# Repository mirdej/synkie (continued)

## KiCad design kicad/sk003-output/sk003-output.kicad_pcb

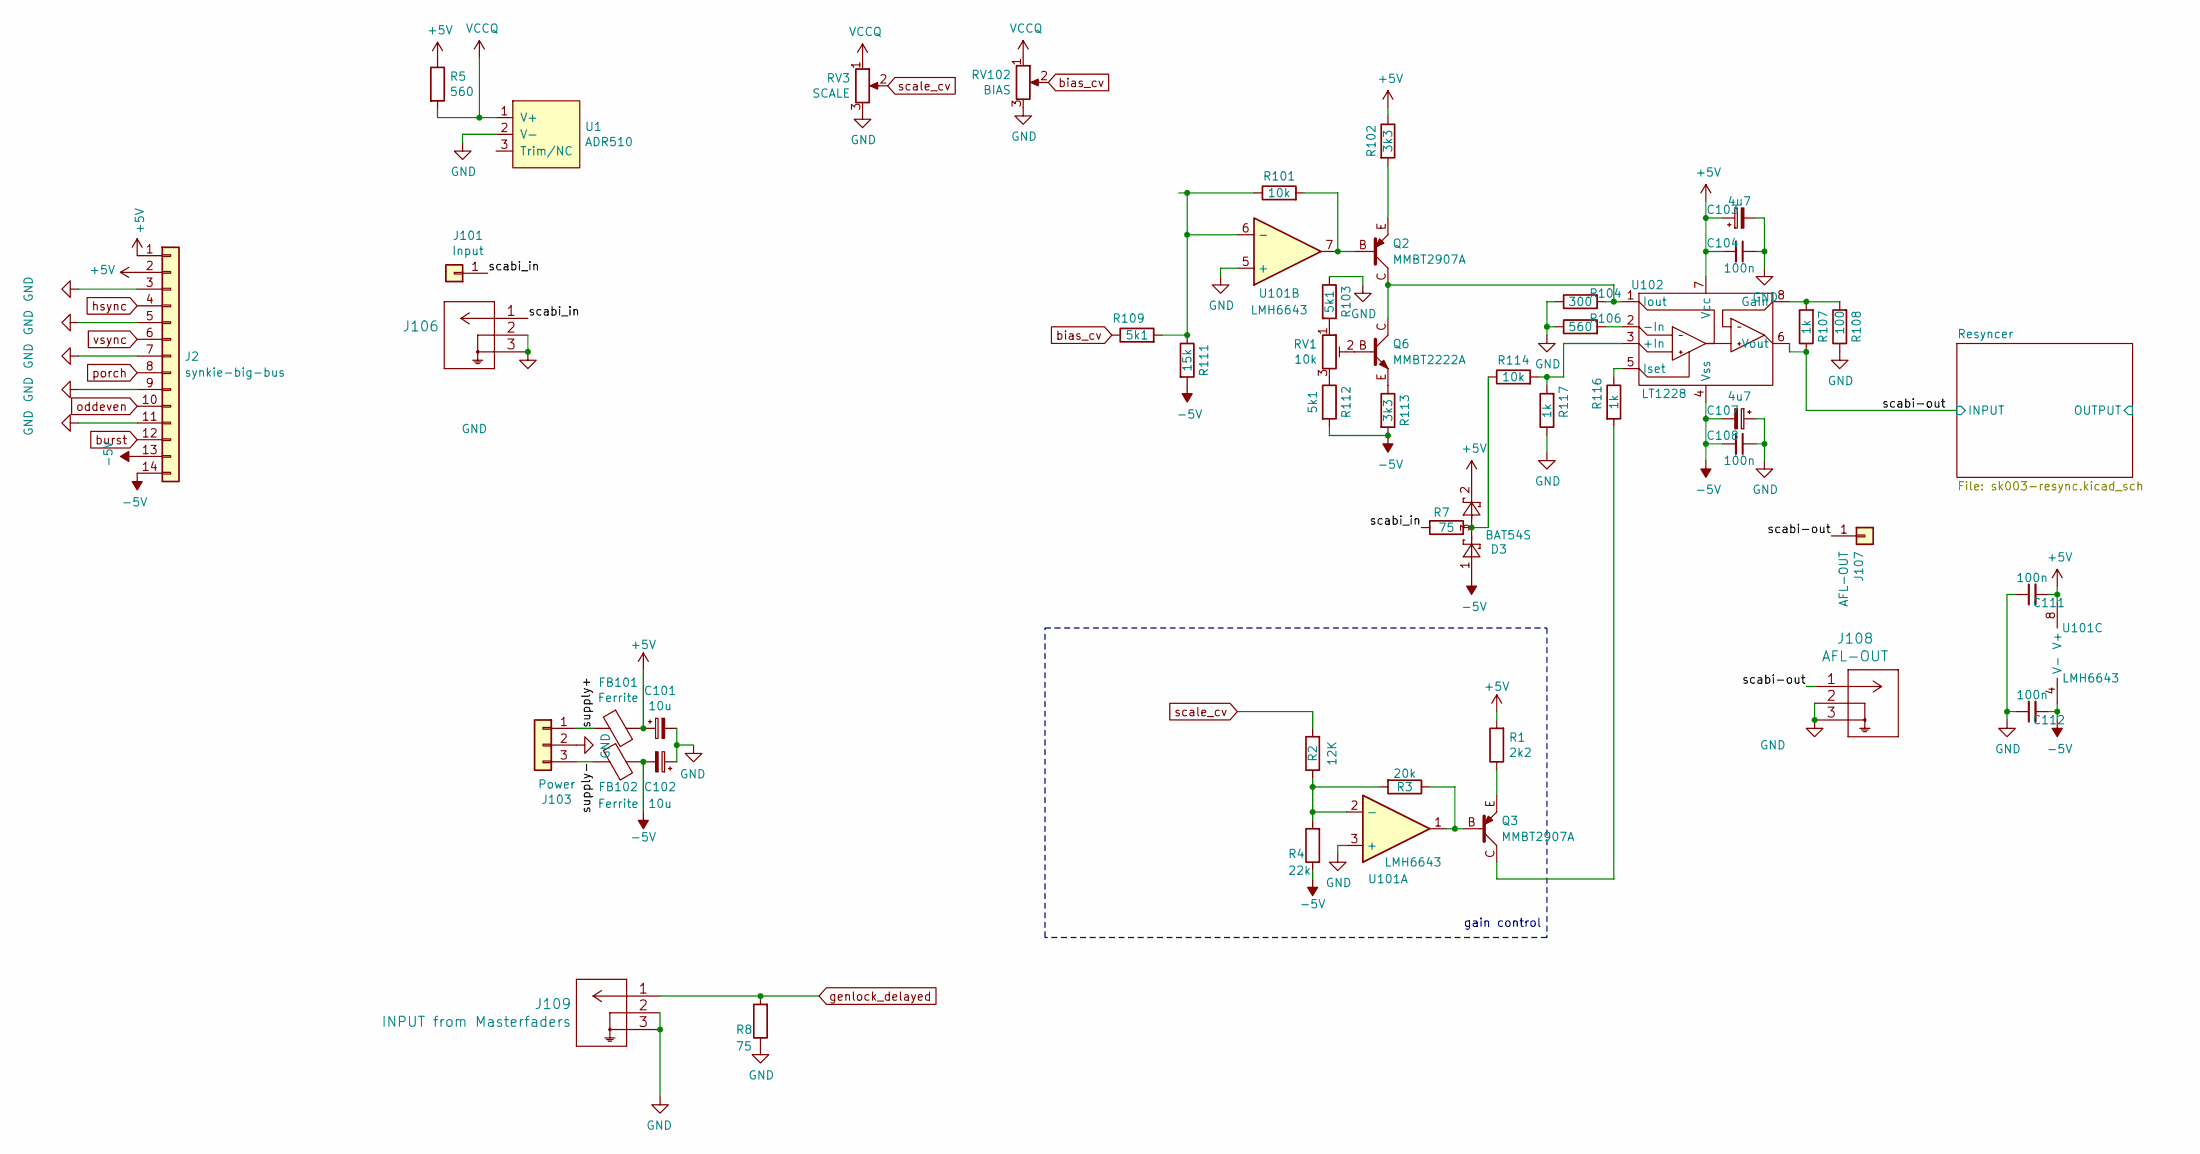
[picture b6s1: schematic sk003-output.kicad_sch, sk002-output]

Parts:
C101, C102: 10u; C_0805_2012Metric; LCSC C15850
C103, C107: 4u7; C_1206_3216Metric; LCSC C29823
C104, C108, C111, C112: 100n; C_0603_1608Metric; LCSC C14663
D3: BAT54S; SOT-23; LCSC C8592
FB101, FB102: Ferrite; L_0805_2012Metric_Pad1.15x1.40mm_HandSolder; LCSC C1017
J2: synkie-big-bus; IDC-Header_2x07_P2.54mm_Vertical
J101: Input; TestPoint_THTPad_D4.0mm_Drill2.0mm
J103: Power; Molex_KK-254_AE-6410-03A_1x03_P2.54mm_Vertical
J106: INPUT from Mixbus; TE_UMCC_2337019-1
J107: AFL-OUT; TestPoint_THTPad_D4.0mm_Drill2.0mm
J108: AFL-OUT; TE_UMCC_2337019-1; LCSC C5137195
J109: INPUT from Masterfaders; TE_UMCC_2337019-1; LCSC C5137195
Q2, Q3: MMBT2907A; SOT-23_BEC; LCSC C40752
Q6: MMBT2222A; SOT-23_BEC; LCSC C82460
R1: 2k2; R_0603_1608Metric; LCSC C4190
R2: 12K; R_0603_1608Metric; LCSC C22790
R3: 20k; R_0603_1608Metric; LCSC C4184
R4: 22k; R_0603_1608Metric; LCSC C31850
R5, R106: 560; R_0603_1608Metric; LCSC C23204
R7, R8: 75; R_0603_1608Metric; LCSC C4275
R101, R114: 10k; R_0603_1608Metric; LCSC C25804
R102, R113: 3k3; R_0603_1608Metric; LCSC C22978
R103, R109, R112: 5k1; R_0603_1608Metric; LCSC C23186
R104: 300; R_0603_1608Metric; LCSC C23025
R107, R116, R117: 1k; R_0603_1608Metric; LCSC C21190
R108: 100; R_0603_1608Metric; LCSC C22775
R111: 15k; R_0603_1608Metric; LCSC C22809
RV1: 10k; Potentiometer_Bourns_3296Y_Vertical; LCSC C25804
RV3: SCALE; Potentiometer_Alps_RK09L_Single_Horizontal
RV102: BIAS; Potentiometer_Alps_RK09L_Single_Horizontal
U1: ADR510; SOT-23; LCSC C77651
U101: LMH6643; VSSOP-8_3x3mm_P0.65mm; LCSC C478382
U102: LT1228; SOIC-8_3.9x4.9mm_P1.27mm

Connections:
+5V: C101.1, C103.1, C104.2, C111.2, D3.2, FB101.2, J2.1, J2.2, R1.2, R5.1, R102.1, U101.8 (V+), U102.7 (Vcc); also elsewhere on the board
-5V: C102.2, C107.2, C108.2, C112.2, D3.1, FB102.2, J2.13, J2.14, R4.1, R111.2, R112.2, R113.2, U101.4 (V-), U102.4 (Vss); also elsewhere on the board
/scabi-out: J107.1, J108.1, R107.1, U102.6 (Vout); also elsewhere on the board
/scabi_in: J101.1, J106.1, R7.1
/supply+: FB101.1, J103.1
/supply-: FB102.1, J103.3
GND: C101.2, C102.1, C103.2, C104.1, C107.1, C108.1, C111.1, C112.1, J2.3, J2.5, J2.7, J2.9, J2.11, J103.2, J106.2, J106.3, J108.2, J108.3, J109.2, J109.3, R8.1, R103.1, R104.1, R106.1, R108.1, R117.1, RV3.3, RV102.3, U1.2 (V-), U101.3 (+), U101.5 (+); also elsewhere on the board
unnamed: D3.3, R7.2, R114.1
unnamed: Q2.B, R101.2, U101.7
unnamed: Q2.E, R102.2
unnamed: Q3.B, R3.1, U101.1
unnamed: Q3.C, R116.2
unnamed: Q3.E, R1.1
unnamed: Q6.B, RV1.2
unnamed: Q6.E, R113.1
unnamed: R103.2, RV1.1
unnamed: R112.1, RV1.3
unnamed: R2.1, R3.2, R4.2, U101.2 (-)
unnamed: R101.1, R109.2, R111.1, U101.6 (-)
unnamed: R114.2, R117.2, U102.3 (+In)
unnamed: R106.2, U102.2 (-In)
unnamed: R107.2, R108.2, U102.8 (Gain)
unnamed: Q2.C, Q6.C, R104.2, U102.1 (Iout)
unnamed: R116.1, U102.5 (Iset)
VCCQ: R5.2, RV3.1, RV102.1, U1.1 (V+)
bias_cv: R109.1, RV102.2
burst: J2.12; also elsewhere on the board
genlock_delayed: J109.1, R8.2; also elsewhere on the board
hsync: J2.4; also elsewhere on the board
oddeven: J2.10
porch: J2.8; also elsewhere on the board
scale_cv: R2.2, RV3.2
vsync: J2.6

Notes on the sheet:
gain control

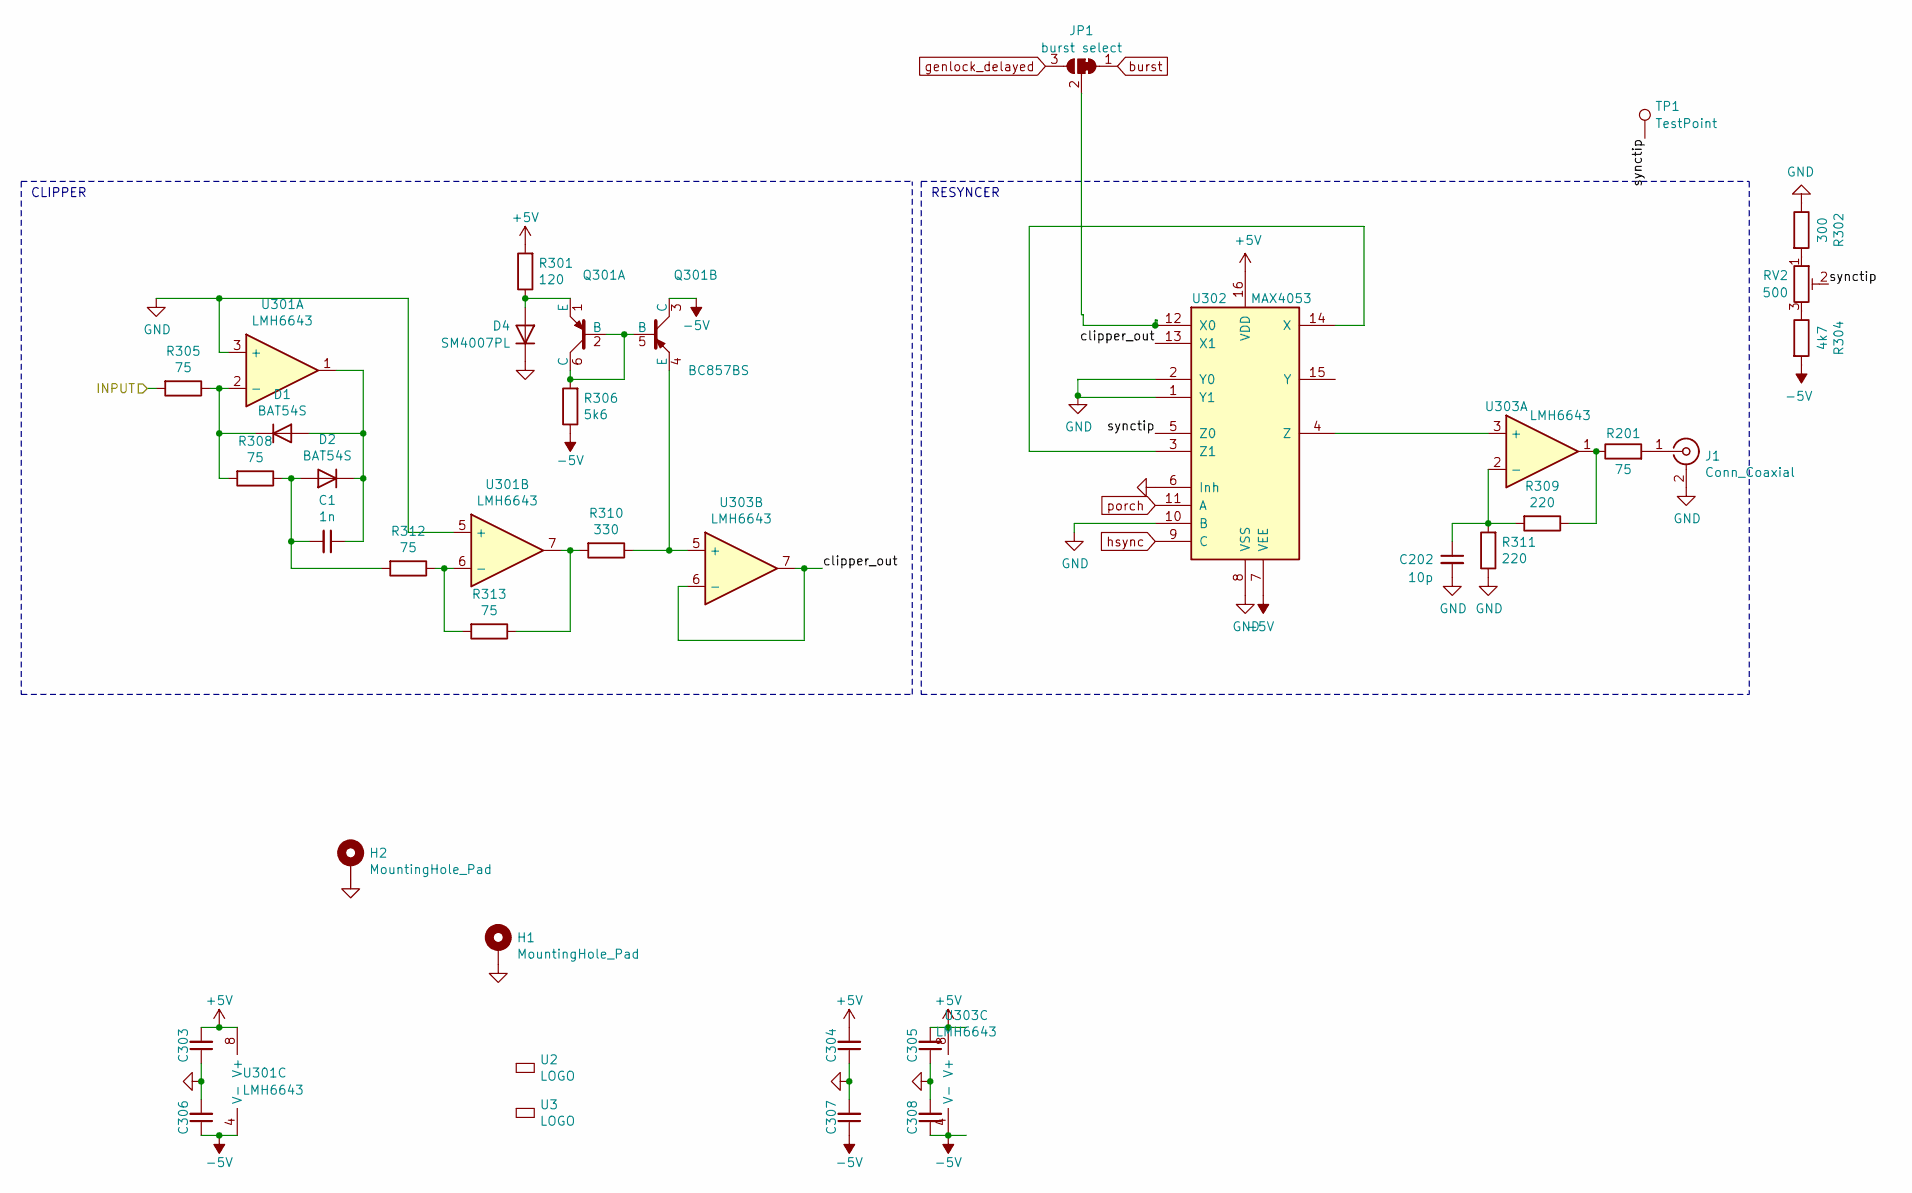
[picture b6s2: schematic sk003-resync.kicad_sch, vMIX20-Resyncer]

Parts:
C1: 1n; C_0603_1608Metric; LCSC C1588
C202: 10p; C_0603_1608Metric; LCSC C1634
C303, C304, C305, C306, C307, C308: 100n; C_0603_1608Metric; LCSC C14663
D1, D2: BAT54S; SOT-23; LCSC C8592
D4: SM4007PL; D_SOD-123F; LCSC C64898
H1: MountingHole_Pad; MountingHole_2.7mm_M2.5_DIN965_Pad
H2: MountingHole_Pad; CrocodileGroundPad
J1: Conn_Coaxial; BNC_Aliexpress
JP1: burst select; SolderJumper-3_P1.3mm_Bridged12_Pad1.0x1.5mm_NumberLabels
Q301: BC857BS; SOT-363_SC-70-6_Handsoldering; LCSC C22381405
R201, R305, R308, R312, R313: 75; R_0603_1608Metric; LCSC C4275
R301: 120; R_0603_1608Metric; LCSC C22787
R302: 300; R_0603_1608Metric; LCSC C23025
R304: 4k7; R_0603_1608Metric; LCSC C23162
R306: 5k6; R_0603_1608Metric; LCSC C23189
R309, R311: 220; R_0603_1608Metric; LCSC C22962
R310: 330; R_0603_1608Metric; LCSC C23138
RV2: 500; Potentiometer_Bourns_3314J_Vertical; LCSC C123873
TP1: TestPoint; TestPoint_Pad_2.0x2.0mm
U2: LOGO; logo_anyma
U3: LOGO; OSHW-Logo2_9.8x8mm_SilkScreen
U301, U303: LMH6643; VSSOP-8_3x3mm_P0.65mm; LCSC C478382
U302: MAX4053; SOIC-16_3.9x9.9mm_P1.27mm; LCSC C1545882

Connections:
+5V: C303.2, C304.2, C305.2, R301.2, U301.8 (V+), U302.16 (VDD), U303.8 (V+); also elsewhere on the board
-5V: C306.1, C307.1, C308.1, Q301.3 (C), R304.2, R306.1, U301.4 (V-), U302.7 (VEE), U303.4 (V-); also elsewhere on the board
/Resyncer/clipper_out: U302.13 (X1), U303.6 (-), U303.7
/Resyncer/synctip: RV2.2, TP1.1, U302.5 (Z0)
/scabi-out: R305.2; also elsewhere on the board
GND: C202.2, C303.1, C304.1, C305.1, C306.2, C307.2, C308.2, D4.1 (K), H1.1, H2.1, J1.2 (Ext), R302.1, R311.1, U301.3 (+), U301.5 (+), U302.1 (Y1), U302.2 (Y0), U302.6 (Inh), U302.8 (VSS), U302.10 (B); also elsewhere on the board
unnamed: C1.1, D1.2 (A), D2.1 (K), U301.1
unnamed: D1.1 (K), R305.1, R308.2, U301.2 (-)
unnamed: C1.2, D2.2 (A), R308.1, R312.2
unnamed: D4.2 (A), Q301.1 (E), R301.1
unnamed: J1.1 (In), R201.2
unnamed: JP1.2 (C), U302.12 (X0)
unnamed: Q301.2 (B), Q301.5 (B), Q301.6 (C), R306.2
unnamed: Q301.4 (E), R310.1, U303.5 (+)
unnamed: R201.1, R309.1, U303.1
unnamed: R302.2, RV2.1
unnamed: R304.1, RV2.3
unnamed: R310.2, R313.1, U301.7
unnamed: R312.1, R313.2, U301.6 (-)
unnamed: U302.3 (Z1), U302.14 (X)
unnamed: U302.4 (Z), U303.3 (+)
unnamed: C202.1, R309.2, R311.2, U303.2 (-)
burst: JP1.1 (A); also elsewhere on the board
genlock_delayed: JP1.3 (B); also elsewhere on the board
hsync: U302.9 (C); also elsewhere on the board
porch: U302.11 (A); also elsewhere on the board

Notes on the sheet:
CLIPPER
RESYNCER

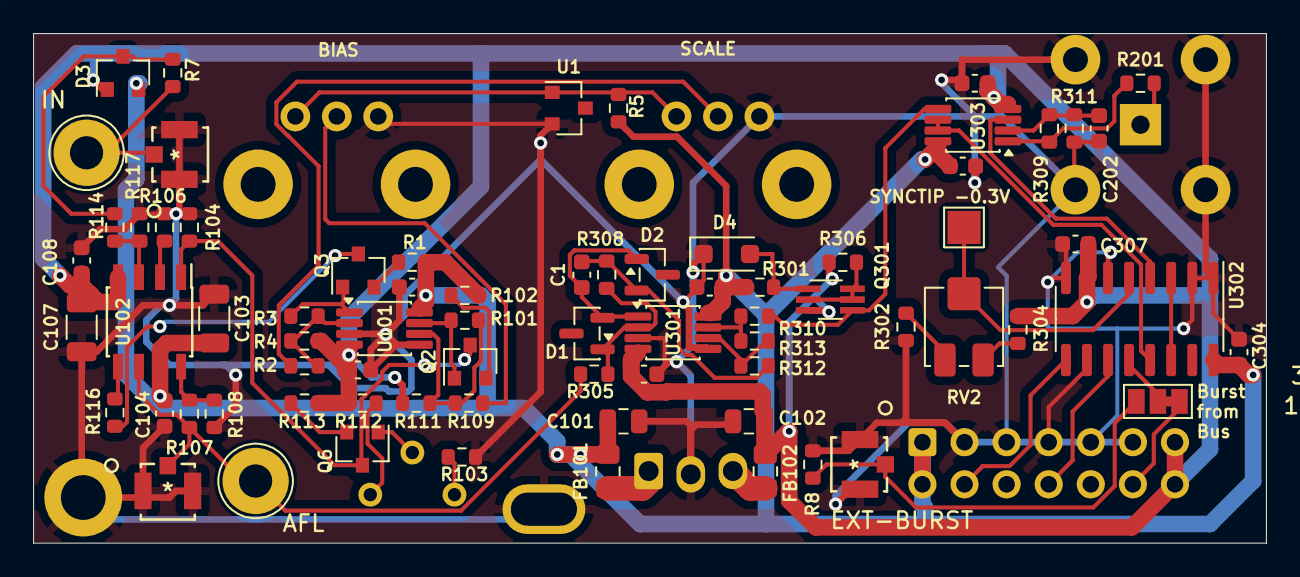
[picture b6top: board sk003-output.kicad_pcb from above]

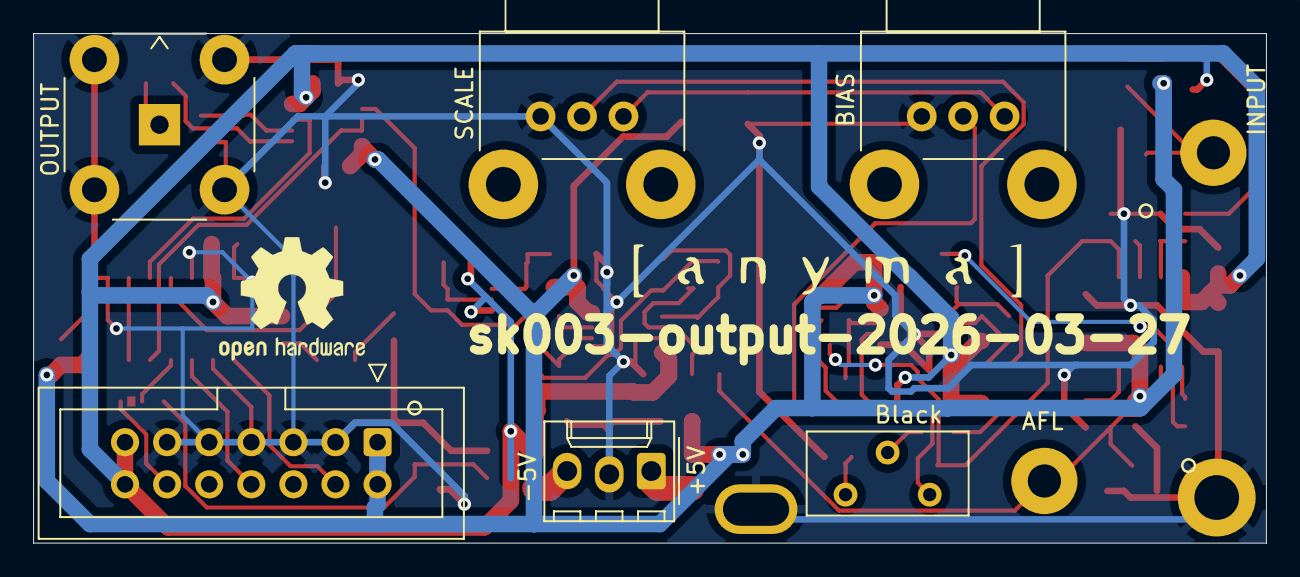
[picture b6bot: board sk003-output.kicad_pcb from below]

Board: 2 copper layers, 74.4 x 30.8 mm, 83 parts (8 on the bottom side), 49 nets.
